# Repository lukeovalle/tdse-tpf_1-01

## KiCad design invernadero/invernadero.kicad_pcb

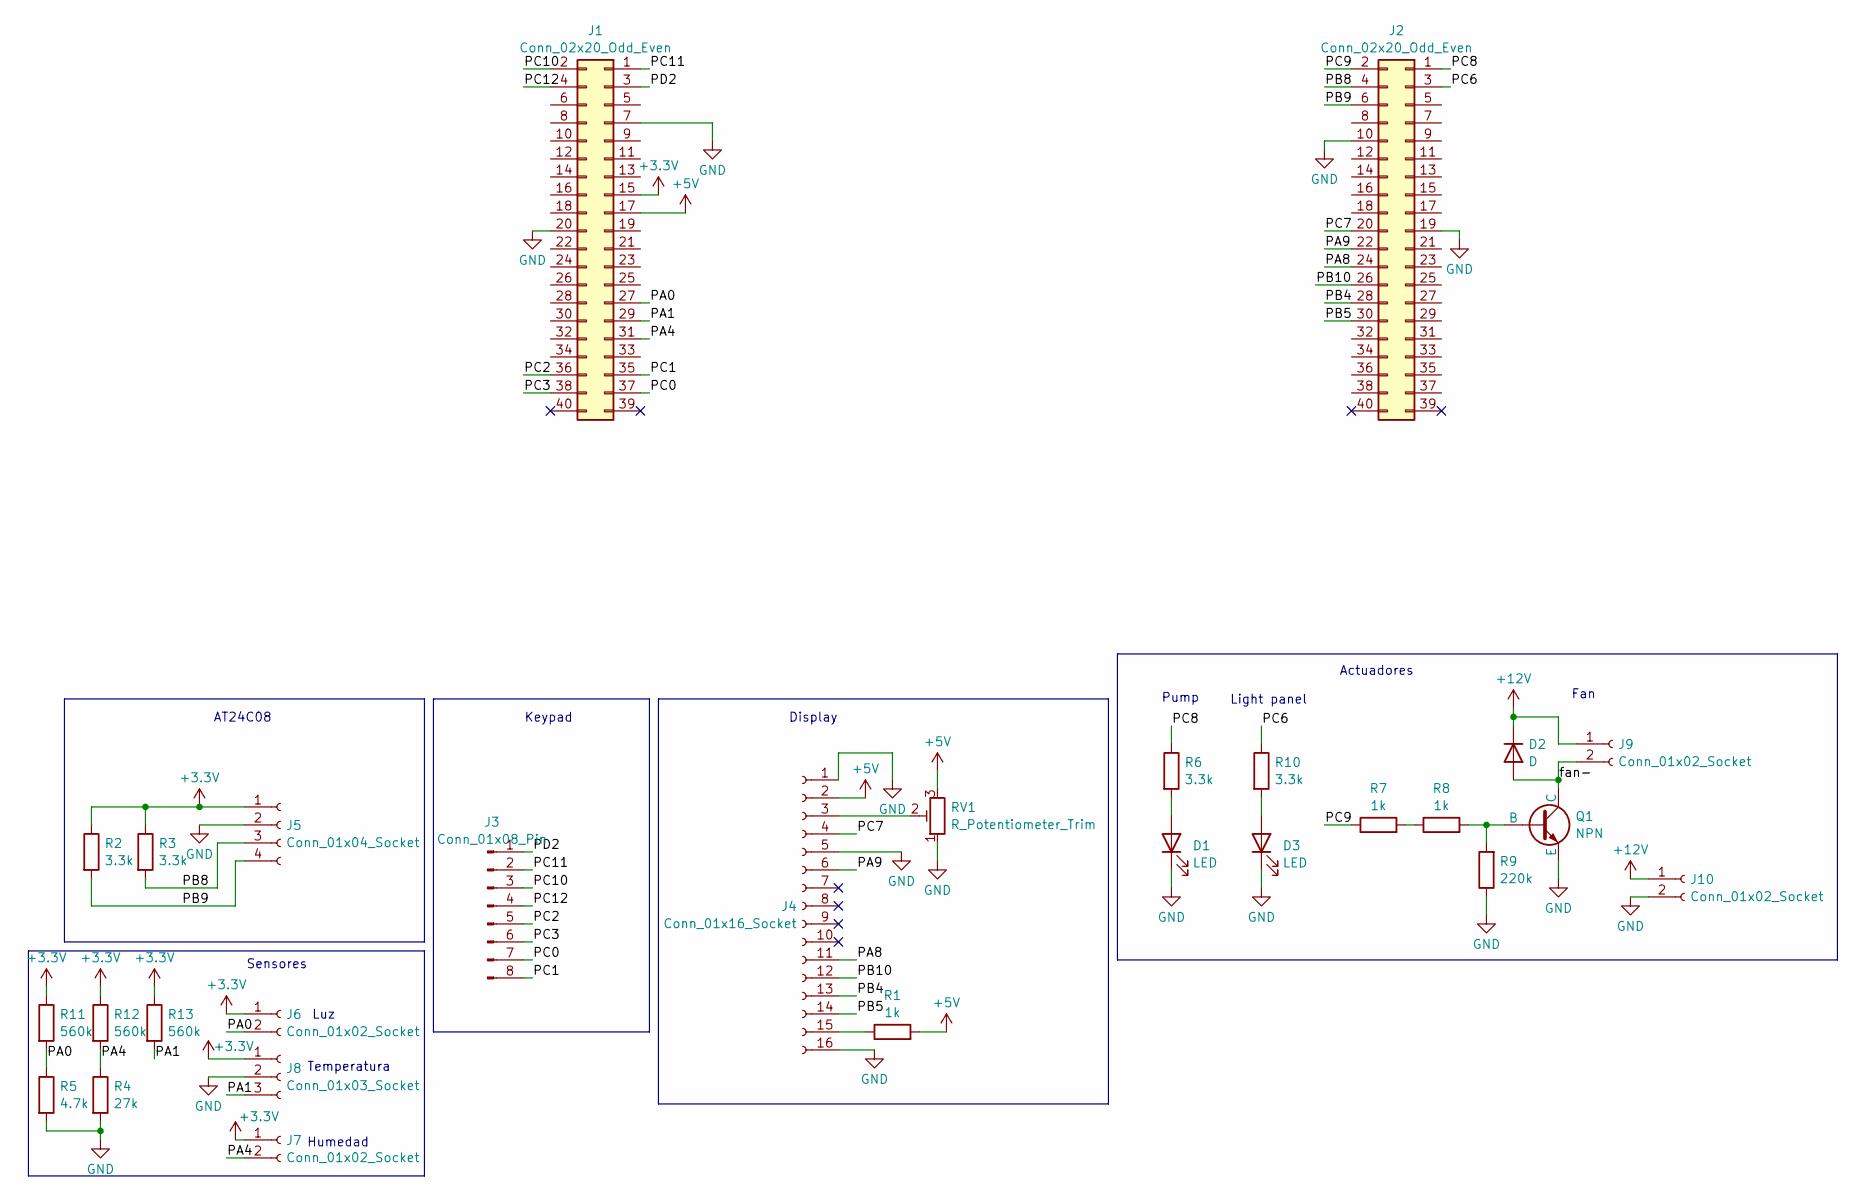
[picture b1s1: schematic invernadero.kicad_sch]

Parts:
D1, D3: LED; LED_D3.0mm_Clear
D2: D; D_DO-41_SOD81_P7.62mm_Horizontal
J1, J2: Conn_02x20_Odd_Even; PinSocket_2x20_P2.54mm_Vertical
J3: Conn_01x08_Pin; PinHeader_1x08_P2.54mm_Vertical
J4: Conn_01x16_Socket; PinSocket_1x16_P2.54mm_Vertical
J5: Conn_01x04_Socket; PinSocket_1x04_P2.54mm_Vertical
J6, J7: Conn_01x02_Socket; PinSocket_1x02_P2.54mm_Vertical
J8: Conn_01x03_Socket; PinSocket_1x03_P2.54mm_Vertical
J9, J10: Conn_01x02_Socket; TerminalBlock_CUI_TB007-508-02_1x02_P5.08mm_Horizontal
Q1: NPN; TO-92_Inline_Wide
R1, R7, R8: 1k; R_Axial_DIN0204_L3.6mm_D1.6mm_P5.08mm_Horizontal
R2, R3, R6, R10: 3.3k; R_Axial_DIN0204_L3.6mm_D1.6mm_P5.08mm_Horizontal
R4: 27k; R_Axial_DIN0207_L6.3mm_D2.5mm_P7.62mm_Horizontal
R5: 4.7k; R_Axial_DIN0207_L6.3mm_D2.5mm_P7.62mm_Horizontal
R9: 220k; R_Axial_DIN0207_L6.3mm_D2.5mm_P7.62mm_Horizontal
R11, R12, R13: 560k; R_Axial_DIN0207_L6.3mm_D2.5mm_P7.62mm_Horizontal
RV1: R_Potentiometer_Trim; Potentiometer_Bourns_3386P_Vertical

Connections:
+3.3V: J1.15, J5.1, J6.1, J7.1, J8.1, R2.1, R3.1, R11.1, R12.1, R13.1
+5V: J1.17, J4.2, R1.2, RV1.3
+12V: D2.1 (K), J9.1, J10.1
/PA0: J1.27, J6.2, R5.1, R11.2
/PA1: J1.29, J8.3, R13.2
/PA4: J1.31, J7.2, R4.1, R12.2
/PA8: J2.24, J4.11
/PA9: J2.22, J4.6
/PB4: J2.28, J4.13
/PB5: J2.30, J4.14
/PB8: J2.4, J5.3, R3.2
/PB9: J2.6, J5.4, R2.2
/PB10: J2.26, J4.12
/PC0: J1.37, J3.7
/PC1: J1.35, J3.8
/PC2: J1.36, J3.5
/PC3: J1.38, J3.6
/PC6: J2.3, R10.1
/PC7: J2.20, J4.4
/PC8: J2.1, R6.1
/PC9: J2.2, R7.1
/PC10: J1.2, J3.3
/PC11: J1.1, J3.2
/PC12: J1.4, J3.4
/PD2: J1.3, J3.1
/fan-: D2.2 (A), J9.2, Q1.1 (C)
GND: D1.1 (K), D3.1 (K), J1.7, J1.20, J2.10, J2.19, J4.1, J4.5, J4.16, J5.2, J8.2, J10.2, Q1.3 (E), R4.2, R5.2, R9.1, RV1.1
unnamed: D1.2 (A), R6.2
unnamed: D3.2 (A), R10.2
unnamed: J4.3, RV1.2
unnamed: J4.15, R1.1
unnamed: Q1.2 (B), R8.2, R9.2
unnamed: R7.2, R8.1

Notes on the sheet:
Fan
Keypad
Humedad
Display
Temperatura
AT24C08
Luz
Sensores
Actuadores
Light panel
Pump

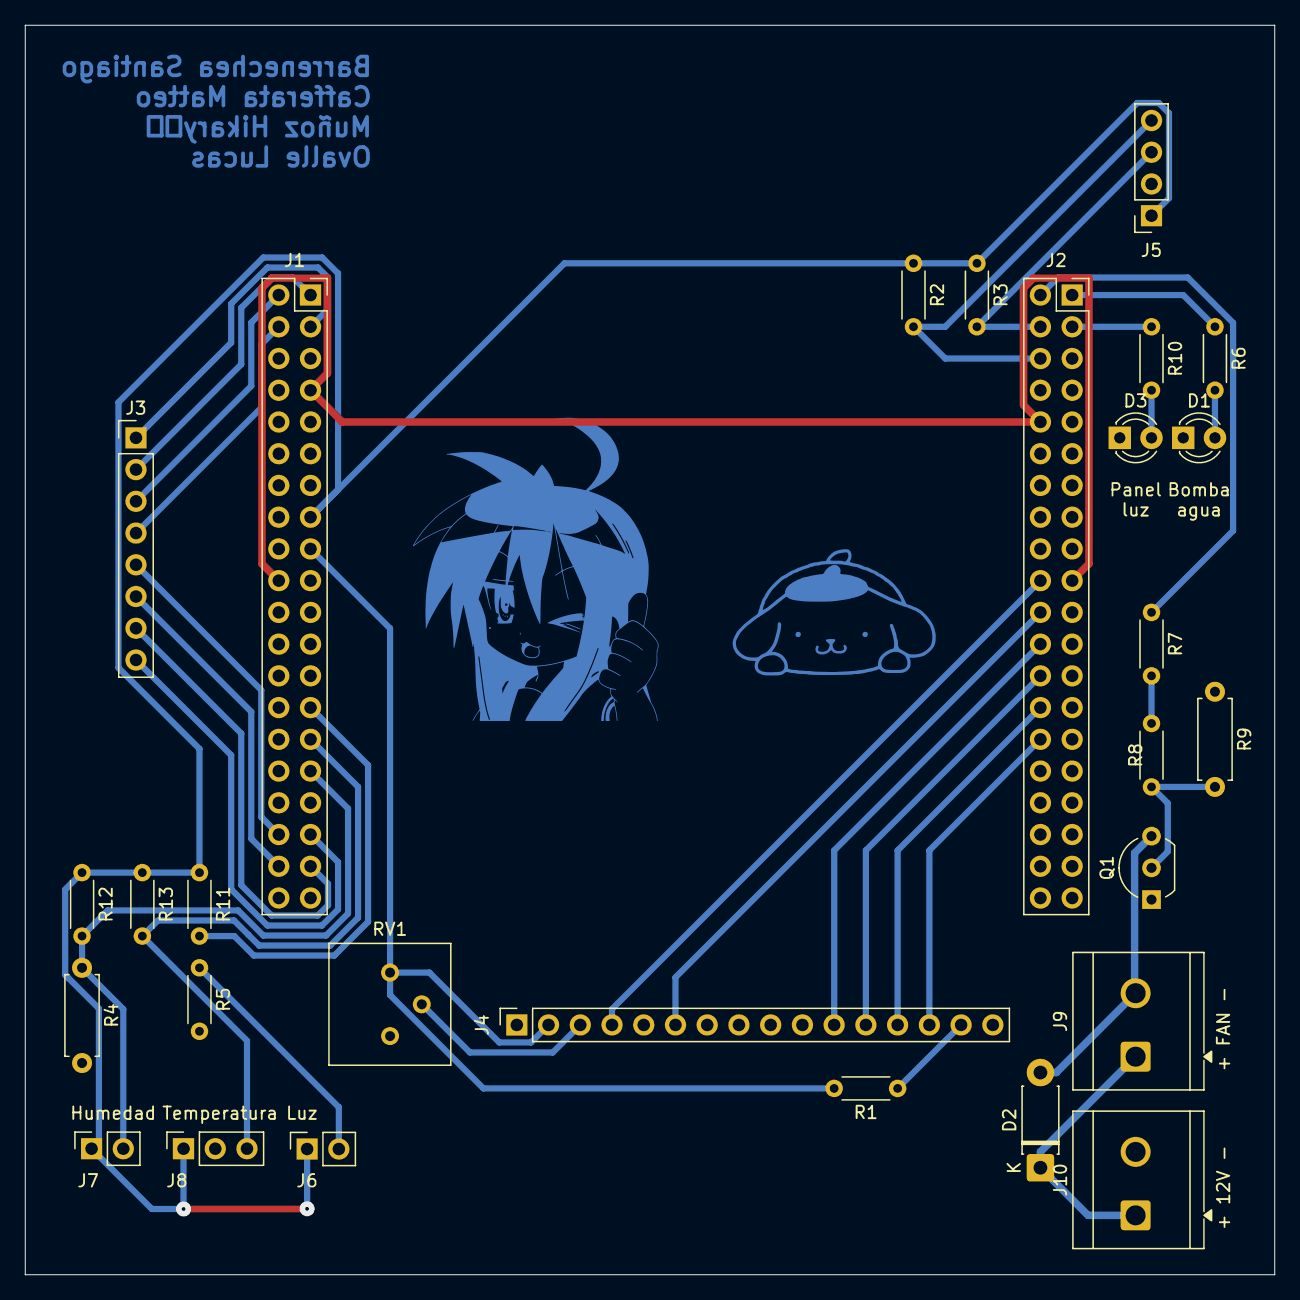
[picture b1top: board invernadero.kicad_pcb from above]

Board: 2 copper layers, 100.0 x 100.0 mm, 28 parts (0 on the bottom side), 33 nets.

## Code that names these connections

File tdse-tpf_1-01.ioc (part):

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Mcu.Name=STM32F103R(8-B)Tx
Mcu.Package=LQFP64
Mcu.UserName=STM32F103RBTx
PA0-WKUP.GPIOParameters=GPIO_Label
PA0-WKUP.GPIO_Label=LIGHT_SENSOR
PA0-WKUP.Signal=ADCx_IN0
PA1.GPIOParameters=GPIO_Label
PA1.GPIO_Label=TEMP_SENSOR
PA1.Signal=ADCx_IN1
PA13.GPIOParameters=GPIO_Label
PA13.GPIO_Label=TMS
PA13.Mode=Serial_Wire
PA13.Signal=SYS_JTMS-SWDIO
PA14.GPIOParameters=GPIO_Label
PA14.GPIO_Label=TCK
PA14.Mode=Serial_Wire
PA14.Signal=SYS_JTCK-SWCLK
PA2.GPIOParameters=GPIO_Speed,GPIO_PuPd,GPIO_Label,GPIO_Mode
PA2.GPIO_Label=USART_TX
PA2.GPIO_Mode=GPIO_MODE_AF_PP
PA2.GPIO_PuPd=GPIO_NOPULL
PA2.GPIO_Speed=GPIO_SPEED_FREQ_LOW
PA2.Mode=Asynchronous
PA2.Signal=USART2_TX
PA3.GPIOParameters=GPIO_Speed,GPIO_PuPd,GPIO_Label,GPIO_Mode
PA3.GPIO_Label=USART_RX
PA3.GPIO_Mode=GPIO_MODE_AF_PP
PA3.GPIO_PuPd=GPIO_NOPULL
PA3.GPIO_Speed=GPIO_SPEED_FREQ_LOW
PA3.Mode=Asynchronous
PA3.Signal=USART2_RX
PA4.GPIOParameters=GPIO_Label
PA4.GPIO_Label=HUMIDITY_SENSOR
PA4.Signal=ADCx_IN4
PA8.GPIOParameters=GPIO_PuPd,GPIO_Label
PA8.GPIO_Label=DISPLAY_D4
PA8.GPIO_PuPd=GPIO_PULLDOWN
PA8.Signal=GPIO_Output
PA9.GPIOParameters=GPIO_PuPd,GPIO_Label
PA9.GPIO_Label=DISPLAY_E
PA9.GPIO_PuPd=GPIO_PULLDOWN
PA9.Signal=GPIO_Output
PB10.GPIOParameters=GPIO_PuPd,GPIO_Label
PB10.GPIO_Label=DISPLAY_D5
PB10.GPIO_PuPd=GPIO_PULLDOWN
PB10.Signal=GPIO_Output
PB3.GPIOParameters=GPIO_Label
PB3.GPIO_Label=SWO
PB3.Signal=SYS_JTDO-TRACESWO
PB4.GPIOParameters=GPIO_PuPd,GPIO_Label
PB4.GPIO_Label=DISPLAY_D6
PB4.GPIO_PuPd=GPIO_PULLDOWN
PB4.Signal=GPIO_Output
PB5.GPIOParameters=GPIO_PuPd,GPIO_Label
PB5.GPIO_Label=DISPLAY_D7
PB5.GPIO_PuPd=GPIO_PULLDOWN
PB5.Signal=GPIO_Output
PB8.GPIOParameters=GPIO_Speed
PB8.GPIO_Speed=GPIO_SPEED_FREQ_HIGH
PB8.Mode=I2C
PB8.Signal=I2C1_SCL
PB9.Mode=I2C
PB9.Signal=I2C1_SDA
PC0.GPIOParameters=PinState,GPIO_PuPd,GPIO_Label
PC0.GPIO_Label=ROW2
PC0.GPIO_PuPd=GPIO_PULLDOWN
PC0.PinState=GPIO_PIN_RESET
PC0.Signal=GPIO_Output
PC1.GPIOParameters=GPIO_PuPd,GPIO_Label
PC1.GPIO_Label=ROW1
PC1.GPIO_PuPd=GPIO_PULLDOWN
PC1.Signal=GPIO_Output
PC10.GPIOParameters=GPIO_PuPd,GPIO_Label
PC10.GPIO_Label=COL2
PC10.GPIO_PuPd=GPIO_PULLDOWN
PC10.Signal=GPIO_Input
PC11.GPIOParameters=GPIO_PuPd,GPIO_Label
PC11.GPIO_Label=COL3
PC11.GPIO_PuPd=GPIO_PULLDOWN
PC11.Signal=GPIO_Input
PC12.GPIOParameters=GPIO_PuPd,GPIO_Label
PC12.GPIO_Label=COL1
PC12.GPIO_PuPd=GPIO_PULLDOWN
PC12.Signal=GPIO_Input
PC14-OSC32_IN.Mode=LSE-External-Oscillator
PC14-OSC32_IN.Signal=RCC_OSC32_IN
PC15-OSC32_OUT.Mode=LSE-External-Oscillator
PC15-OSC32_OUT.Signal=RCC_OSC32_OUT
PC2.GPIOParameters=GPIO_PuPd,GPIO_Label
PC2.GPIO_Label=ROW4
PC2.GPIO_PuPd=GPIO_PULLDOWN
PC2.Signal=GPIO_Output
PC3.GPIOParameters=GPIO_PuPd,GPIO_Label
PC3.GPIO_Label=ROW3
PC3.GPIO_PuPd=GPIO_PULLDOWN
PC3.Signal=GPIO_Output
PC6.GPIOParameters=GPIO_PuPd,GPIO_Label
PC6.GPIO_Label=ACTUATOR_LIGHT_PANEL
PC6.GPIO_PuPd=GPIO_PULLDOWN
PC6.Signal=GPIO_Output
PC7.GPIOParameters=GPIO_PuPd,GPIO_Label
PC7.GPIO_Label=DISPLAY_RS
PC7.GPIO_PuPd=GPIO_PULLDOWN
PC7.Signal=GPIO_Output
PC8.GPIOParameters=GPIO_PuPd,GPIO_Label
PC8.GPIO_Label=ACTUATOR_PUMP
PC8.GPIO_PuPd=GPIO_PULLDOWN
PC8.Signal=GPIO_Output
PC9.GPIOParameters=GPIO_PuPd,GPIO_Label
PC9.GPIO_Label=ACTUATOR_FAN
PC9.GPIO_PuPd=GPIO_PULLDOWN
PC9.Signal=GPIO_Output
PD0-OSC_IN.Mode=HSE-External-Clock-Source
PD0-OSC_IN.Signal=RCC_OSC_IN
PD1-OSC_OUT.Mode=HSE-External-Clock-Source
PD1-OSC_OUT.Signal=RCC_OSC_OUT
PD2.GPIOParameters=GPIO_PuPd,GPIO_Label
PD2.GPIO_Label=COL4
PD2.GPIO_PuPd=GPIO_PULLDOWN
PD2.Signal=GPIO_Input
RCC.SYSCLKFreq_VALUE=48000000
RCC.SYSCLKSource=RCC_SYSCLKSOURCE_PLLCLK
board=NUCLEO-F103RB
boardIOC=true

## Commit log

2025-09-14 inicio proyecto stm32
2025-09-14 inicio circuito kicad
2025-09-14 propuesta.txt
2025-10-03 light sensor started. i2c and adc pins assigned
2025-10-15 Implementación del sensor de luz, falta leer el ADC
2025-10-31 definición de función de lectura de sensor de luz
2025-11-07 sensor de luz funciona, iniciado sensor de humedad
2025-11-12 Unificación de lógica de los sensores, medición de ADC
2025-11-19 Rangos de sensores modificados. Eliminado módulo de humedad.
2025-11-28 Lectura correcta de sensores
2025-12-10 Módulo I2C iniciado.
2025-12-16 I2C Compila.
2026-01-21 I2C: función para escribir una página en memoria y cambios en la máquina de estados
2026-01-22 I2C: Módulo terminado
2026-01-22 Definición de interfaz de memoria
2026-01-24 Implementadas funciones de manejo de memoria externa
2026-01-26 buffer circular para escribir a memoria externa. funciones auxiliares de memoria escriben al buffer
2026-01-27 task I2C usa el buffer de escritura y definida interfaz de lectura para I2C
2026-01-27 Errores arreglados en I2C y memoria
2026-01-28 Arreglados problemas de dirección de memoria y de dispositivo en I2C
2026-01-28 Debugging de lectura/escritura de memoria
2026-01-29 keypad
2026-01-29 Renombrar task_sensor a task_keypad para evitar conflictos
2026-01-29 Eliminar viejos archivos task_sensor
2026-01-30 Posibilidad de meter retardos en escaneo
2026-01-30 Arreglado error en la máquina de estados y callbacks correctos
2026-01-30 I2C FUNCIONA
2026-01-30 Removida tarea de prueba y loggers, memoria eeprom empieza en 0x00
2026-01-30 Iniciada tarea de clock
2026-01-30 Escaneos multiples evitan multiplicidad de tecla pulsada
2026-01-30 Codigo base (tps viejos)
2026-01-30 Maquina de estados esquematica
2026-01-31 máquina de estados de clock implementada
2026-01-31 WCET cambiado para no reiniciar el contador de ciclos. Reloj funciona.
2026-01-31 funciones vacías de configuración de fecha y hora
2026-01-31 código copiado de la rama botonera
2026-01-31 cambiados pines de conexión de display y botonera
2026-02-03 funciones para configurar fecha y hora
2026-02-03 Clock terminado
2026-02-03 Validación de memoria externa llena
2026-02-03 placa con conexiones para display y botonera
2026-02-04 reestructuracion
2026-02-04 pequeño comentario
2026-02-04 Diseño de PCB completo
2026-02-04 esquemático
2026-02-04 maquina de estados 10%
2026-02-04 maquina de estados 20%
2026-02-04 maquina de estados 40%
2026-02-04 maquina de estados 50%
2026-02-04 maquina de estados 60%
2026-02-05 borrado archivo lock innecesario
2026-02-05 copiados cambios de rama botonera
2026-02-05 Máquina de estados de actuadores. Añadidos pines en archivo ioc.
2026-02-05 Cola circular
2026-02-05 Empezar lectura de botones
2026-02-06 Lectura de botones
2026-02-06 Eventos al menu
2026-02-06 Lectura de botones completa (espero)
2026-02-06 Funciones de conversión entre timestamp y date_time_t
2026-02-06 Bug corregido en conversión entre timestamp y datetime
2026-02-06 FSM esqueleto completado
2026-02-06 limpieza update
2026-02-06 limpieza
2026-02-07 Logica de scroll implementada
2026-02-09 Arregladas funciones de conversión entre timestamp y date_time
2026-02-09 cambios en el pcb
2026-02-09 Velocidad de clock aumentada a 20 MHz, flag en mem_buffer agregado
2026-02-09 append_to_buffer para lectura y escritura
2026-02-09 ignorar configuraciones del ide y archivos temporales de kicad en el repo
2026-02-10 Terminado de implementar buffer para lectura
2026-02-10 Solucionados algunos bugs de lectura y escritura en memoria. macros MIN y MAX
2026-02-10 memoria funciona !!!
2026-02-10 Modificado footprint de led y path de fan más ancho
2026-02-10 path del fan más ancho
2026-02-11 Lógica del controlador implementada. Añadido panel de luz. Configuración guarda horas diarias de luz, valor mínimo de luz y temperaturas por día/noche. PCB actualizado.
2026-02-11 ignorar pdf
2026-02-19 Solucionado error de concurrencia en sensores. Sensores miden resistencia
2026-02-19 PCB reordenado. Pistas ensanchadas.
2026-02-19 Cálculo de porcentaje de humedad y cálculo de temperatura
2026-02-21 Medición de humedad.
2026-02-22 Normalize line endings to LF
2026-02-22 Cambios FSM
2026-02-23 Comenatrios configuracion
2026-02-23 Comenatrios lecturas
2026-02-24 Displays cfg agregados
2026-02-24 Configuración completa
2026-02-24 Bugs menores
2026-02-24 include stdbool
2026-02-24 sensor de luz calibrado
2026-02-27 Correcciones: pines keypad y display; errores de copilación
2026-02-27 tareas de menu y keypad agregadas
2026-02-28 Teclado funciona
2026-02-28 Emprolijado de mensajes por menu_display
2026-02-28 Corrección de displays para números
2026-03-02 Display configuraciones
2026-03-02 Corregido bug en nombre de función
2026-03-02 Corregido bug display_con
2026-03-02 Display muestras (falta el tema del tiempo de la muestra)
2026-03-02 Solucionados varios warnings
2026-03-02 pantalla inicial se muestra correctamente
2026-03-02 Menú lee y escribe correctamente las configuraciones
2026-03-03 Máquina de estados del menú espera a que se lean los datos de memoria
2026-03-03 Varios warnings solucionados, código emprolijado
2026-03-03 Menús reordenados, agregada opción de limpiar logs
2026-03-03 Velocidad de reloj aumentada a 72MHz. Solucionado problema de desbordamiento de reloj.
2026-03-03 Solucionado overflow en WCET
2026-03-10 Máquina de estados para display. keypad con tick counter
2026-03-11 Solucionados errores y warnings
2026-03-14 DisplayDiff
2026-03-14 compila
2026-03-14 pines de salida en high speed
2026-03-14 máquina de estados del keypad es solo una
2026-03-19 Elimino delay, oversampling que si tengo FMS es incesaria y scan una fila por ciclo
2026-03-19 Uso una sola FMS para controlar todos los botones ya que en la matriz solo se puede pulsar uno a la vez y reduzco x16 el tiempo
2026-03-22 Correcciones de Santaigo
2026-03-22 keypad compila
2026-03-22 PCB actualizado
2026-03-22 PCB actualizado 2
2026-03-22 PCB actualizado 3
2026-03-23 Keypad escanea de a una tecla por iteración
2026-03-23 WCET reducido
2026-03-24 Display imprime correctamente la segunda línea. Tiempos de ejecución reducidos
2026-03-24 Resistencia máxima en los sensores
2026-03-24 Velocidad de reloj y systick modificados
2026-03-27 Agregada documentación
2026-03-27 Solucionadas impresiones de texto
2026-03-27 Solucionado problema de pantalla. Funciona todo
